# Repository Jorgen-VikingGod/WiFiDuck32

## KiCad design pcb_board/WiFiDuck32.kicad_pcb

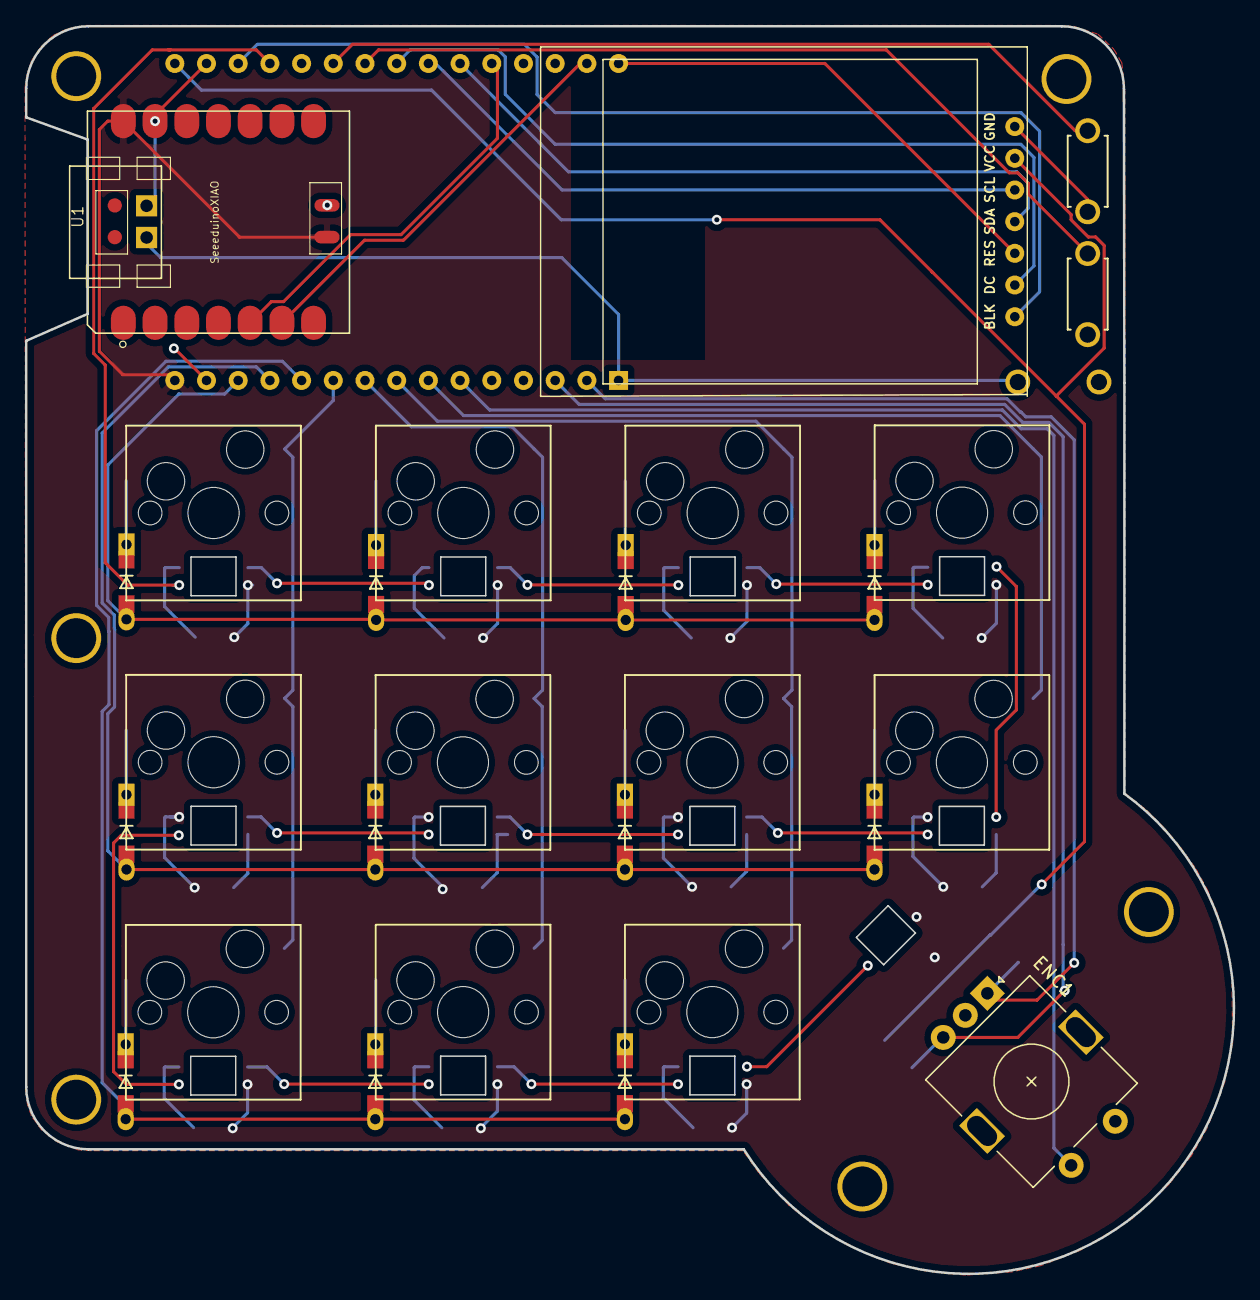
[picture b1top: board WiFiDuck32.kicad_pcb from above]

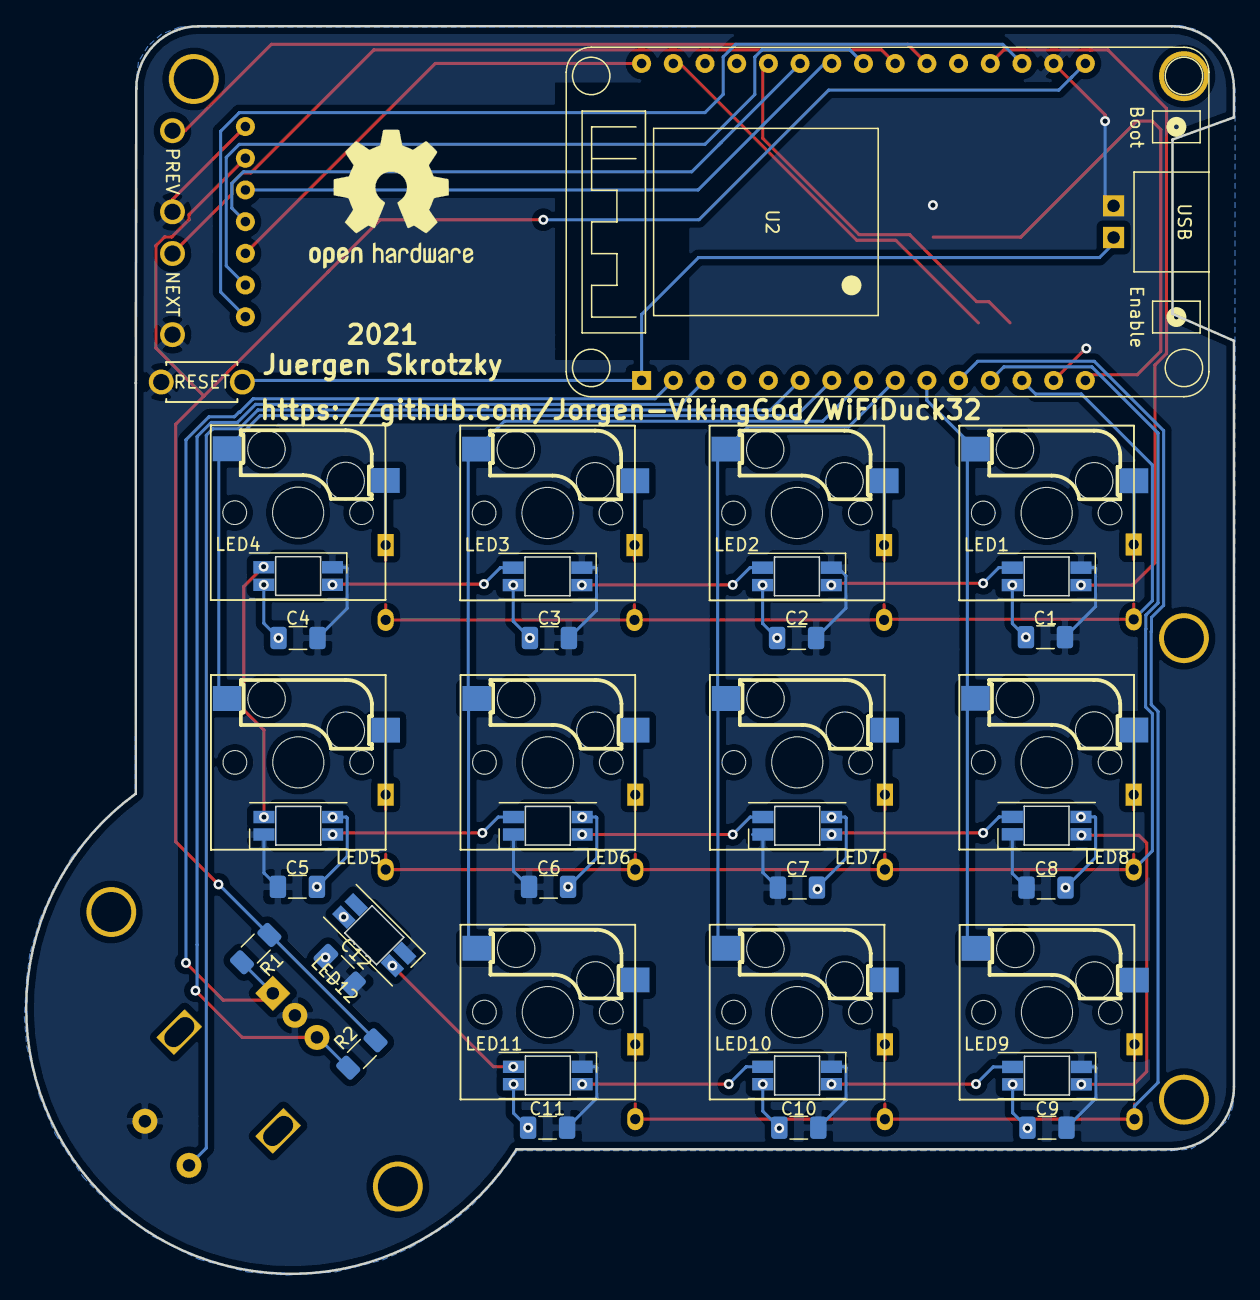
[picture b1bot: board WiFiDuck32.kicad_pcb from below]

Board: 2 copper layers, 96.8 x 100.0 mm, 63 parts (28 on the bottom side), 46 nets.

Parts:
C1, C2, C3, C4, C5, C6, C7, C8, C9, C10, C11, C12: 0.1uF; C_1206_3216Metric_Pad1.33x1.80mm_HandSolder
D1, D2, D3, D4, D5, D6, D7, D8, D9, D10, D11: DIODE; D3_TH_SMD_v2
ENC1: Rotary_Encoder_Switch; RotaryEncoder_Alps_EC11E-Switch_Vertical_H20mm
HOLE_M3, HOLE_M3#2, HOLE_M3#3, HOLE_M3#4, HOLE_M3#5, HOLE_M3#6: VAL**; HOLE_M3
J1: TFT_Conn; ips_tft_240x240
J_GND: Conn_01x01_Female; PinHeader_1x01_P2.54mm_Vertical
J_RST: Conn_01x01_Female; PinHeader_1x01_P2.54mm_Vertical
LED1, LED2, LED3, LED4, LED5, LED6, LED7, LED8, LED9, LED10, LED11, LED12: YS-SK6812MINI-E
R1, R2: 10k; R_1206_3216Metric_Pad1.30x1.75mm_HandSolder
SW1, SW2, SW3, SW4, SW5, SW6, SW7, SW8, SW9, SW10, SW11: SW_PUSH; CherryMX_Hotswap_single
SW_BTN1: SW_BTN1; ResetSW_1side
SW_BTN2: SW_BTN2; ResetSW_1side
SW_RST1: SW_RST; ResetSW_1side
U1: SeeeduinoXIAO; Seeeduino XIAO-MOUDLE14P-2.54-21X17.8MM
U2: ESP32_DevKit_V1_DOIT; esp32_devkit_v1_doit

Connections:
+3V3: J1.2, R1.1, R2.2, U2.16
+5V: C1.1, C2.1, C3.1, C4.1, C5.2, C6.2, C7.2, C8.2, C9.1, C10.1, C11.1, C12.1, LED1.1, LED2.1, LED3.1, LED4.1, LED5.1, LED6.1, LED7.1, LED8.1, LED9.1, LED10.1, LED11.1, LED12.1, U1.14, U1.15, U2.15
BTN1: SW_BTN1.1, U2.21
BTN2: SW_BTN2.1, U2.22
CLK: ENC1.A, R1.2, U2.2
DT: ENC1.B, R2.1, U2.3
GND: C1.2, C2.2, C3.2, C4.2, C5.1, C6.1, C7.1, C8.1, C9.2, C10.2, C11.2, C12.2, ENC1.C, ENC1.S2, J1.1, J_GND.1, LED1.3, LED2.3, LED3.3, LED4.3, LED5.3, LED6.3, LED7.3, LED8.3, LED9.3, LED10.3, LED11.3, LED12.3, SW_BTN1.2, SW_BTN2.2, SW_RST1.2, U1.13, U1.16, U1.20, U2.14, U2.17
LED1: LED1.4, U2.19
unnamed: D1.1, SW1.1
unnamed: D2.1, SW2.1
unnamed: D3.1, SW3.1
unnamed: D4.1, SW4.1
unnamed: D5.1, SW5.1
unnamed: D6.1, SW6.1
unnamed: D7.1, SW7.1
unnamed: D8.1, SW8.1
unnamed: D9.1, SW9.1
unnamed: D10.1, SW10.1
unnamed: D11.1, SW11.1
unnamed: LED1.2, LED2.4
unnamed: LED2.2, LED3.4
unnamed: LED3.2, LED4.4
unnamed: LED4.2, LED5.4
unnamed: LED5.2, LED6.4
unnamed: LED6.2, LED7.4
unnamed: LED7.2, LED8.4
unnamed: LED8.2, LED9.4
unnamed: LED10.2, LED11.4
unnamed: LED9.2, LED10.4
unnamed: LED11.2, LED12.4
RST: J_RST.1, SW_RST1.1, U1.19, U2.1
SCL: U1.6, U2.29
SDA: U1.5, U2.26
SW: ENC1.S1, U2.6
TFT_BL: J1.7, U2.18
TFT_DC: J1.6, U2.23
TFT_MOSI: J1.4, U2.25
TFT_RST: J1.5, U2.30
TFT_SCLK: J1.3, U2.24
col1: SW1.2, SW5.2, SW9.2, U2.10
col2: SW2.2, SW6.2, SW10.2, U2.9
col3: SW3.2, SW7.2, SW11.2, U2.8
col4: SW4.2, SW8.2, U2.7
row1: D1.2, D2.2, D3.2, D4.2, U2.13
row2: D5.2, D6.2, D7.2, D8.2, U2.12
row3: D9.2, D10.2, D11.2, U2.11

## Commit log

2021-04-23 Add board pcb files
2021-04-23 Add plate pcb files
2021-04-23 Add modified atmega duck files
2021-04-30 Add initial esp32 files
2021-05-02 Add custom encoder and 12s LED
    - rotary encoder or left/right encoder
    - use LED 12 to highlight encoder actions
2021-05-02 Add extensions.json for platformio
2021-05-03 Add display output on starup
2021-05-04 Add Seeeduino XIAO kicad files
2021-05-06 Modify pcbs for seeeduino XIAO
    - replace Arduino Pro Micro by Seeeduino XIAO
2021-05-07 Modify to use TinyUSB
    use TinyUSB_Mouse_and_Keyboard.h by cyborg5
    instead of Keaboard.h and Mouse.h
